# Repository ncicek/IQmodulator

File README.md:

# IQmodulator

A low cost FPGA-based platform for generating RF signals.
It is implemented with more discrete components than a typical SDR with an "all in one" RF transceiver chip. For example the quadrature double-balanced mixer uses hand-wound trifilar transformers.
 As such, it is intended as a learning platform to show the individual components at play.

# Description
The board is designed to plug into the Lattice MachXO3 FPGA starter board.
The FPGA generates the 10-bit baseband I and Q signals. A MAX5853 DAC generates the baseband analog signals which are filtered with a differential 7th order chebyshev. The FPGA PLL is also used to synthesize the quadrature LO which goes to the quadrature mixer in order to upconvert the baseband up to high frequency.

The RTL uses wishbone modules which are heavily based on material from [Gisselquist Technology's blog posts and sample code](https://zipcpu.com).

# PCB:

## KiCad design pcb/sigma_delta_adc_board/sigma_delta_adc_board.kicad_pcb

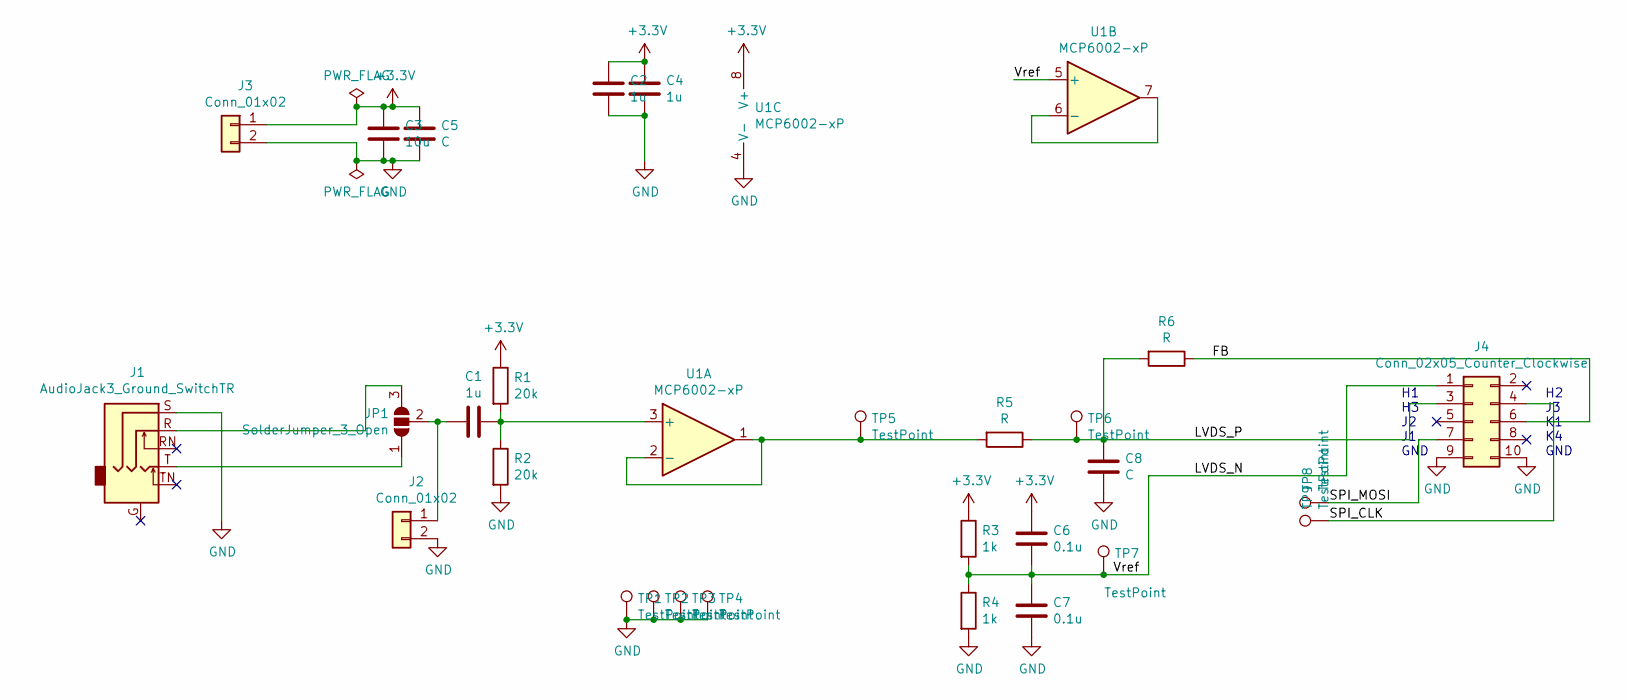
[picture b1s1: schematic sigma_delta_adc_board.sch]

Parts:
C1: 1u; C_Disc_D5.0mm_W2.5mm_P5.00mm
C2, C4: 1u; C_0805_2012Metric_Pad1.18x1.45mm_HandSolder
C3: 10u; C_Disc_D5.0mm_W2.5mm_P5.00mm
C5: C; C_Disc_D5.0mm_W2.5mm_P5.00mm
C6, C7: 0.1u; C_0805_2012Metric_Pad1.18x1.45mm_HandSolder
C8: C; C_0805_2012Metric_Pad1.18x1.45mm_HandSolder
J1: AudioJack3_Ground_SwitchTR; STX-3120-5B
J2, J3: Conn_01x02; PinHeader_1x02_P2.54mm_Vertical
J4: Conn_02x05_Counter_Clockwise; PinSocket_2x05_P2.54mm_Vertical
JP1: SolderJumper_3_Open; SolderJumper-3_P1.3mm_Open_RoundedPad1.0x1.5mm_NumberLabels
R1, R2: 20k; R_0805_2012Metric_Pad1.20x1.40mm_HandSolder
R3, R4: 1k; R_0805_2012Metric_Pad1.20x1.40mm_HandSolder
R5, R6: R; R_0805_2012Metric_Pad1.20x1.40mm_HandSolder
TP1, TP2, TP3, TP4, TP5, TP6, TP7: TestPoint; PinHeader_1x01_P2.54mm_Vertical
TP8, TP9: TestPoint; TestPoint_Pad_D1.0mm
U1: MCP6002-xP; DIP-8_W7.62mm

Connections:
+3V3: C2.2, C3.1, C4.2, C5.1, C6.2, J3.1, R1.1, R3.1, U1.8 (V+)
/FB: J4.6, R6.1
/LVDS_N: C6.1, C7.2, J4.1, R3.2, R4.1, TP7.1, U1.5 (+)
/LVDS_P: C8.2, J4.3, R5.1, R6.2, TP6.1
/SPI_CLK: J4.4, TP9.1
/SPI_MOSI: J4.7, TP8.1
GND: C2.1, C3.2, C4.1, C5.2, C7.1, C8.1, J1.S, J2.2, J3.2, J4.9, J4.10, R2.2, R4.2, TP1.1, TP2.1, TP3.1, TP4.1, U1.4 (V-)
unnamed: C1.1, R1.2, R2.1, U1.3 (+)
unnamed: C1.2, J2.1, JP1.2 (C)
unnamed: J1.R, JP1.3 (B)
unnamed: J1.T, JP1.1 (A)
unnamed: R5.2, TP5.1, U1.1, U1.2 (-)
unnamed: U1.6 (-), U1.7

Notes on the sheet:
H1 H3 J2 J1 GND
H2 J3 K1 K4 GND

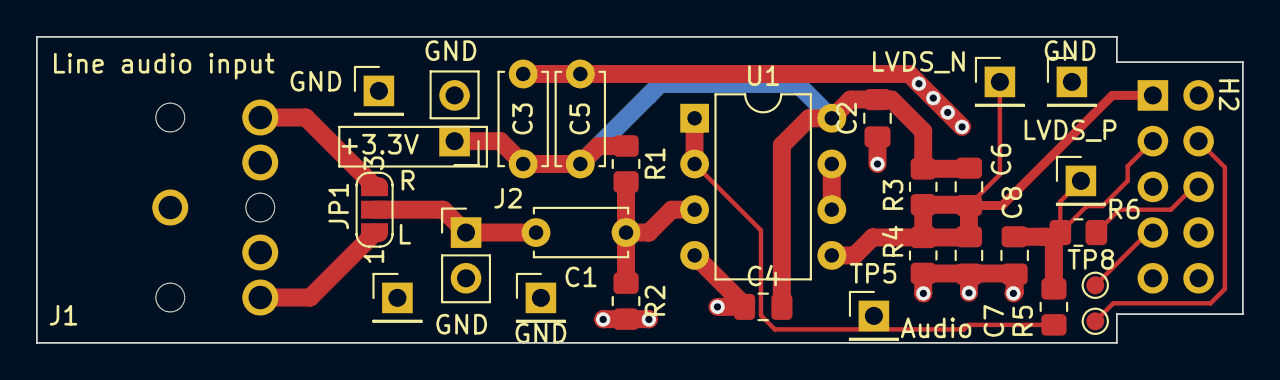
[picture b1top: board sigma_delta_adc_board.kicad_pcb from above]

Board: 2 copper layers, 67.0 x 17.0 mm, 29 parts (1 on the bottom side), 13 nets.

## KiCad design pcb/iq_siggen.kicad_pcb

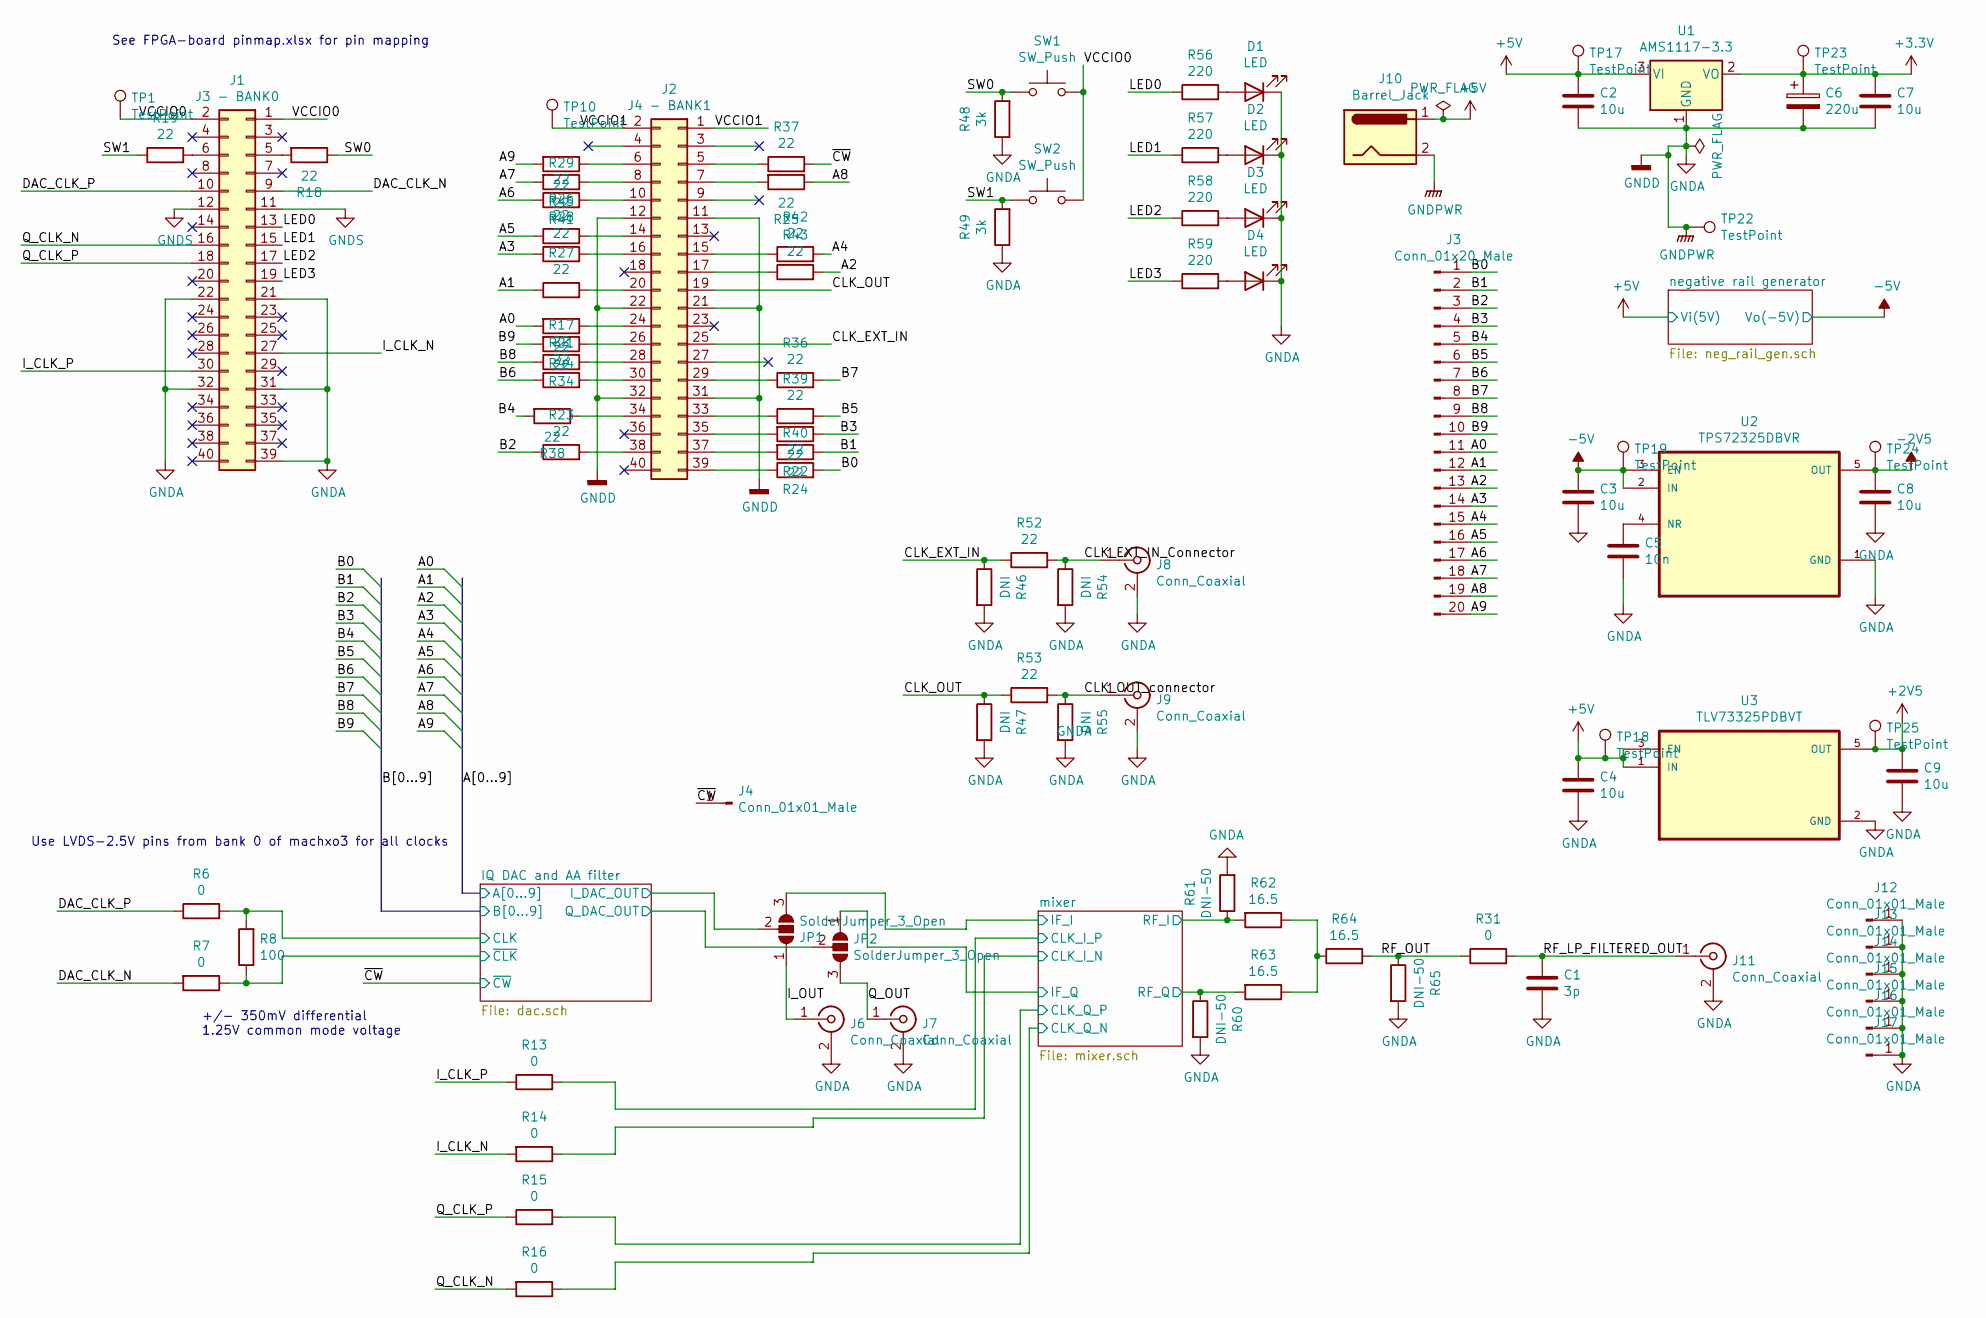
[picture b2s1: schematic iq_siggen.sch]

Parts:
C1: 3p; C_0603_1608Metric
C2, C3, C4, C7, C8, C9: 10u; C_0603_1608Metric; LCSC C19702
C5: 10n; C_0603_1608Metric; LCSC C57112
C6: 220u; CP_EIA-7343-43_Kemet-X_Pad2.25x2.55mm_HandSolder; LCSC C7231
D1, D2, D3, D4: LED; LED_0805_2012Metric_Pad1.15x1.40mm_HandSolder; LCSC C34499
J1: J3 - BANK0; PinHeader_2x20_P2.54mm_Vertical
J2: J4 - BANK1; PinHeader_2x20_P2.54mm_Vertical
J3: Conn_01x20_Male; PinHeader_1x20_P2.54mm_Vertical
J4, J12, J13, J14, J15, J16, J17: Conn_01x01_Male; PinHeader_1x01_P2.54mm_Vertical
J6, J7, J8, J9, J11: Conn_Coaxial; SMA_Samtec_SMA-J-P-X-ST-EM1_EdgeMount_withSTEP
J10: Barrel_Jack; BarrelJack_Horizontal
JP1, JP2: SolderJumper_3_Open; 50ohm_solder_jumper
R6, R7, R13, R14, R15, R16, R31: 0; R_0603_1608Metric; LCSC C21189
R8: 100; R_0603_1608Metric; LCSC C22775
R17, R18, R19, R21, R22, R23, R24, R25, R26, R27, R28, R29, R34, R36, R37, R38, R39, R40, R41, R42, R43, R44, R45, R52, R53: 22; R_0603_1608Metric; LCSC C23345
R46, R47, R54, R55: DNI; R_0603_1608Metric
R48, R49: 3k; R_0603_1608Metric; LCSC C4211
R56, R57, R58, R59: 220; R_0603_1608Metric; LCSC C22962
R60, R61, R65: DNI-50; R_0603_1608Metric
R62, R63, R64: 16.5; R_0603_1608Metric; LCSC C12054
SW1, SW2: SW_Push; SW_PUSH_6mm_H5mm
TP1, TP10, TP17, TP18, TP19, TP22, TP23, TP24, TP25: TestPoint; TestPoint_Pad_D1.5mm
U1: AMS1117-3.3; SOT-223-3_TabPin2; LCSC C6186
U2: TPS72325DBVR; SOT-23-5_HandSoldering; LCSC C69932
U3: TLV73325PDBVT; SOT-23-5_HandSoldering

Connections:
+2V5: C9.1, TP25.1, U3.5 (OUT); also elsewhere on the board
+3V3: C6.1, C7.1, TP23.1, U1.2 (VO); also elsewhere on the board
+5V: C2.1, C4.1, J10.1, TP17.1, TP18.1, U1.3 (VI), U3.1 (IN), U3.3 (EN); also elsewhere on the board
-2V5: C8.1, TP24.1, U2.5 (OUT); also elsewhere on the board
-5V: C3.1, TP19.1, U2.2 (IN), U2.3 (EN); also elsewhere on the board
/A0: J3.11, R44.2; also elsewhere on the board
/A1: J3.12, R27.1; also elsewhere on the board
/A2: J3.13, R43.2; also elsewhere on the board
/A3: J3.14, R28.1; also elsewhere on the board
/A4: J3.15, R42.2; also elsewhere on the board
/A5: J3.16, R26.1; also elsewhere on the board
/A6: J3.17, R29.1; also elsewhere on the board
/A7: J3.18, R41.2; also elsewhere on the board
/A8: J3.19, R25.1; also elsewhere on the board
/A9: J3.20, R45.2; also elsewhere on the board
/B0: J3.1, R40.2; also elsewhere on the board
/B1: J3.2, R24.1; also elsewhere on the board
/B2: J3.3, R23.1; also elsewhere on the board
/B3: J3.4, R22.1; also elsewhere on the board
/B4: J3.5, R38.2; also elsewhere on the board
/B5: J3.6, R39.2; also elsewhere on the board
/B6: J3.7, R21.1; also elsewhere on the board
/B7: J3.8, R36.2; also elsewhere on the board
/B8: J3.9, R17.1; also elsewhere on the board
/B9: J3.10, R34.2; also elsewhere on the board
/CLK_EXT_IN: J2.25, R46.1, R52.1
/CLK_EXT_IN_Connector: J8.1 (In), R52.2, R54.1
/CLK_OUT: J2.19, R47.1, R53.1
/CLK_OUT_connector: J9.1 (In), R53.2, R55.1
/DAC_CLK_N: J1.9, R7.2
/DAC_CLK_P: J1.10, R6.1
/IQ DAC and AA filter/CLK: R6.2, R8.2; also elsewhere on the board
/IQ DAC and AA filter/I_DAC_OUT: JP1.2 (C); also elsewhere on the board
/IQ DAC and AA filter/Q_DAC_OUT: JP2.2 (C); also elsewhere on the board
/IQ DAC and AA filter/~CLK: R7.1, R8.1; also elsewhere on the board
/I_CLK_N: J1.27, R14.2
/I_CLK_P: J1.30, R13.1
/I_OUT: J6.1 (In), JP1.1 (A)
/LED0: J1.13, R56.1
/LED1: J1.15, R57.1
/LED2: J1.17, R58.1
/LED3: J1.19, R59.1
/Q_CLK_N: J1.16, R16.2
/Q_CLK_P: J1.18, R15.1
/Q_OUT: J7.1 (In), JP2.3 (B)
/RF_LP_FILTERED_OUT: C1.1, J11.1 (In), R31.2
/RF_OUT: R31.1, R64.2, R65.1
/SW0: R18.1, R48.2, SW1.1
/SW1: R19.1, R49.2, SW2.1
/VCCIO0: J1.1, J1.2, SW1.2, SW2.2, TP1.1
/VCCIO1: J2.1, J2.2, TP10.1
/mixer/CLK_I_N: R14.1; also elsewhere on the board
/mixer/CLK_I_P: R13.2; also elsewhere on the board
/mixer/CLK_Q_N: R16.1; also elsewhere on the board
/mixer/CLK_Q_P: R15.2; also elsewhere on the board
/mixer/IF_I: JP1.3 (B); also elsewhere on the board
/mixer/IF_Q: JP2.1 (A); also elsewhere on the board
/mixer/RF_I: R61.1, R62.2; also elsewhere on the board
/mixer/RF_Q: R60.1, R63.2; also elsewhere on the board
/~CW: J4.1, R37.2; also elsewhere on the board
GNDA: C1.2, C2.2, C3.2, C4.2, C5.2, C6.2, C7.2, C8.2, C9.2, D1.1 (K), D2.1 (K), D3.1 (K), D4.1 (K), J1.11, J1.12, J1.21, J1.22, J1.31, J1.32, J1.39, J2.11, J2.12, J2.21, J2.22, J2.31, J2.32, J6.2 (Ext), J7.2 (Ext), J8.2 (Ext), J9.2 (Ext), J10.2, J11.2 (Ext), J12.1, J13.1, J14.1, J15.1, J16.1, J17.1, R46.2, R47.2, R48.1, R49.1, R54.2, R55.2, R60.2, R61.2, R65.2, TP22.1, U1.1 (GND), U2.1 (GND), U3.2 (GND); also elsewhere on the board
unnamed: C5.1, U2.4 (NR)
unnamed: D1.2 (A), R56.2
unnamed: D2.2 (A), R57.2
unnamed: D3.2 (A), R58.2
unnamed: D4.2 (A), R59.2
unnamed: J1.5, R18.2
unnamed: J1.6, R19.2
unnamed: J2.5, R37.1
unnamed: J2.6, R45.1
unnamed: J2.7, R25.2
unnamed: J2.8, R41.1
unnamed: J2.10, R29.2
unnamed: J2.14, R26.2
unnamed: J2.15, R42.1
unnamed: J2.16, R28.2
unnamed: J2.17, R43.1
unnamed: J2.20, R27.2
unnamed: J2.24, R44.1
unnamed: J2.26, R34.1
unnamed: J2.28, R17.2
unnamed: J2.29, R36.1
unnamed: J2.30, R21.2
unnamed: J2.33, R39.1
unnamed: J2.34, R38.1
unnamed: J2.35, R22.2
unnamed: J2.37, R24.2
unnamed: J2.38, R23.2
unnamed: J2.39, R40.1
unnamed: R62.1, R63.1, R64.1

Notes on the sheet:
Use LVDS-2.5V pins from bank 0 of machxo3 for all clocks
See FPGA-board pinmap.xlsx for pin mapping
+/- 350mV differential 1.25V common mode voltage

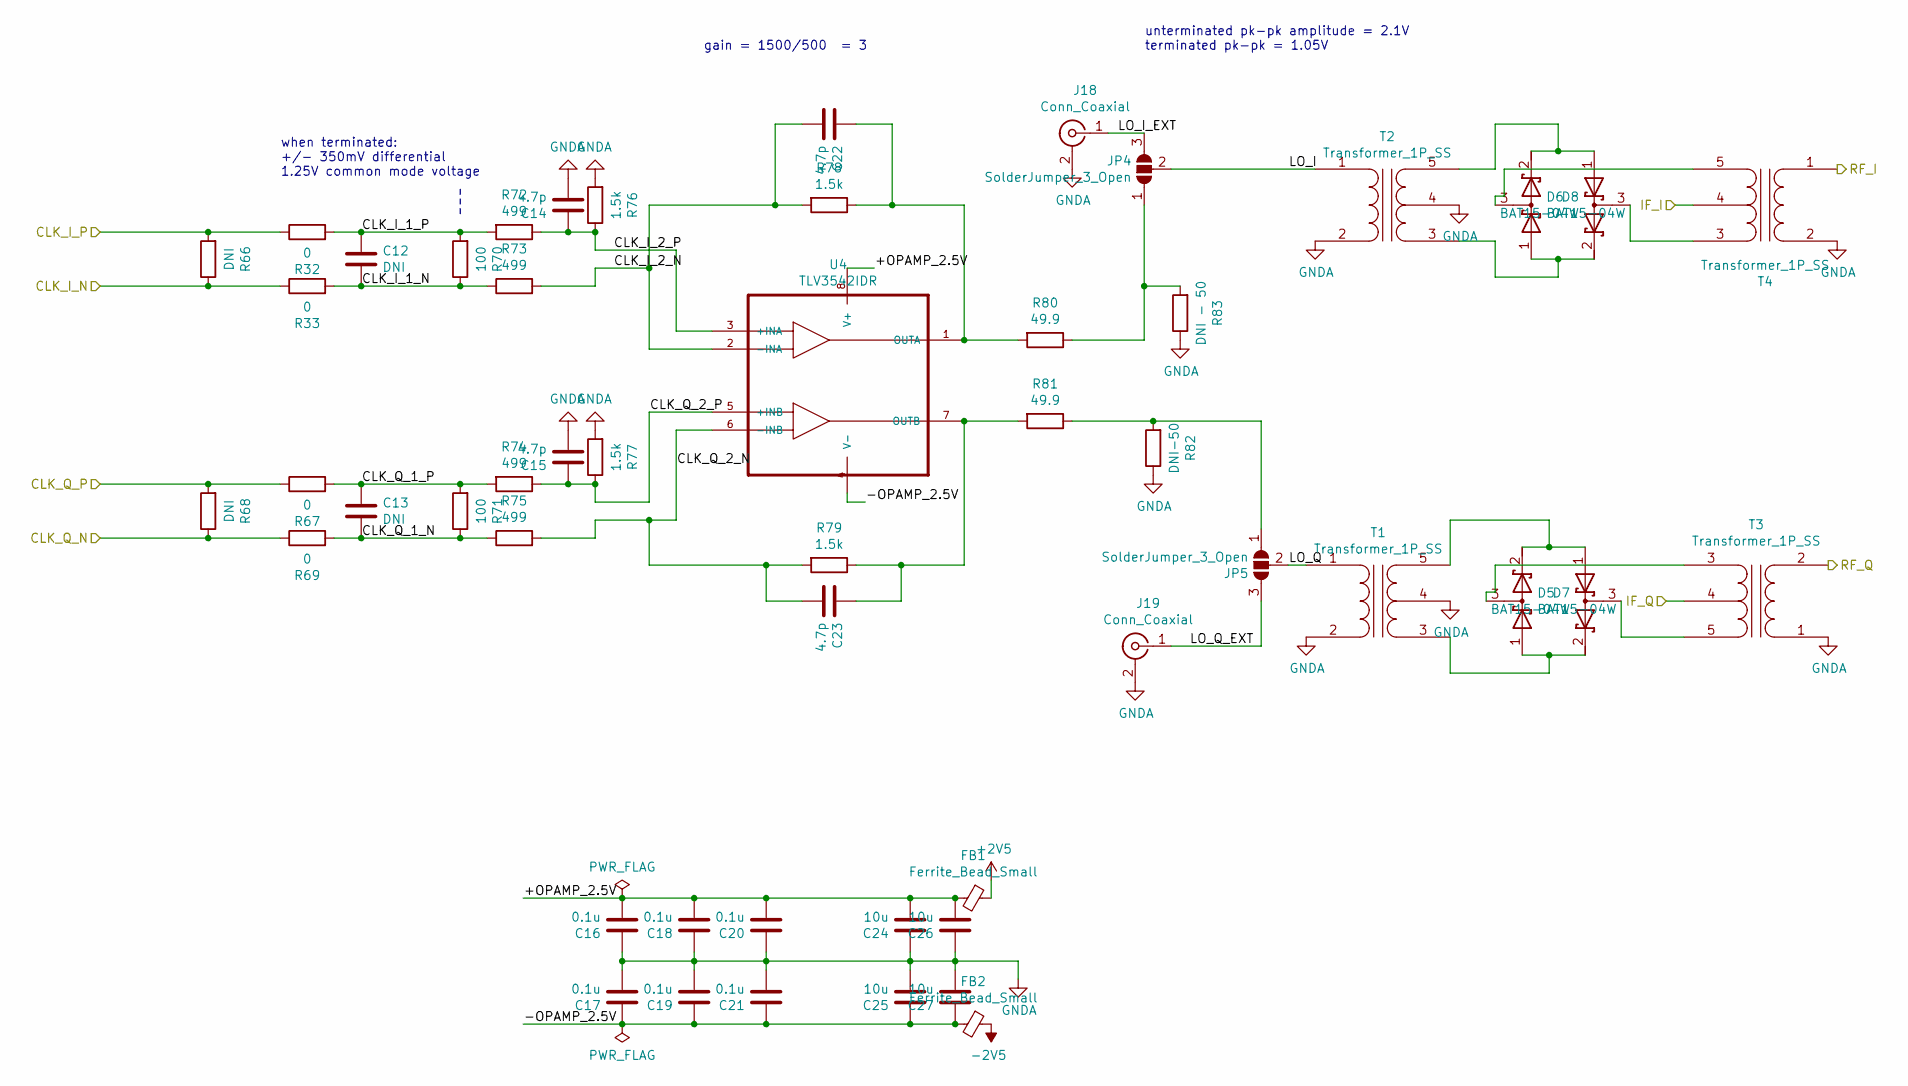
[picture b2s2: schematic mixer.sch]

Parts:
C12, C13: DNI; C_0603_1608Metric
C14, C15, C22, C23: 4.7p; C_0603_1608Metric; LCSC C1669
C16, C17, C18, C19, C20, C21: 0.1u; C_0603_1608Metric; LCSC C14663
C24, C25, C26, C27: 10u; C_0603_1608Metric; LCSC C19702
D5, D6, D7, D8: BAT15-04W; SOT-323_SC-70_Handsoldering
FB1, FB2: Ferrite_Bead_Small; L_0805_2012Metric_Pad1.05x1.20mm_HandSolder; LCSC C19330
J18, J19: Conn_Coaxial; SMA_Samtec_SMA-J-P-X-ST-EM1_EdgeMount_withSTEP
JP4, JP5: SolderJumper_3_Open; 50ohm_solder_jumper
R32, R33, R67, R69: 0; R_0603_1608Metric; LCSC C21189
R66, R68: DNI; R_0603_1608Metric
R70, R71: 100; R_0603_1608Metric; LCSC C22775
R72, R73, R74, R75: 499; R_0603_1608Metric; LCSC C23065
R76, R77, R78, R79: 1.5k; R_0603_1608Metric; LCSC C22843
R80, R81: 49.9; R_0603_1608Metric; LCSC C23185
R82: DNI-50; R_0603_1608Metric
R83: DNI - 50; R_0603_1608Metric
T1, T2, T3, T4: Transformer_1P_SS; trifilar_wound_toroidal_rf_transformer
U4: TLV3542IDR; SOIC-8_3.9x4.9mm_P1.27mm

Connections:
+2V5: FB1.1; also elsewhere on the board
-2V5: FB2.1; also elsewhere on the board
/mixer/+OPAMP_2.5V: C16.2, C18.2, C20.2, C24.2, C26.2, FB1.2, U4.8 (V+)
/mixer/-OPAMP_2.5V: C17.1, C19.1, C21.1, C25.1, C27.1, FB2.2, U4.4 (V-)
/mixer/CLK_I_1_N: C12.2, R33.2, R70.1, R73.1
/mixer/CLK_I_1_P: C12.1, R32.2, R70.2, R72.2
/mixer/CLK_I_2_N: C22.2, R73.2, R78.2, U4.2 (-INA)
/mixer/CLK_I_2_P: C14.1, R72.1, R76.1, U4.3 (+INA)
/mixer/CLK_I_N: R33.1, R66.1; also elsewhere on the board
/mixer/CLK_I_P: R32.1, R66.2; also elsewhere on the board
/mixer/CLK_Q_1_N: C13.2, R69.2, R71.1, R75.1
/mixer/CLK_Q_1_P: C13.1, R67.2, R71.2, R74.2
/mixer/CLK_Q_2_N: C23.2, R75.2, R79.2, U4.6 (-INB)
/mixer/CLK_Q_2_P: C15.1, R74.1, R77.1, U4.5 (+INB)
/mixer/CLK_Q_N: R68.1, R69.1; also elsewhere on the board
/mixer/CLK_Q_P: R67.1, R68.2; also elsewhere on the board
/mixer/IF_I: T4.4 (SC); also elsewhere on the board
/mixer/IF_Q: T3.4 (SC); also elsewhere on the board
/mixer/LO_I: JP4.2 (C), T2.1 (AA)
/mixer/LO_I_EXT: J18.1 (In), JP4.3 (B)
/mixer/LO_Q: JP5.2 (C), T1.1 (AA)
/mixer/LO_Q_EXT: J19.1 (In), JP5.3 (B)
/mixer/RF_I: T4.1 (AA); also elsewhere on the board
/mixer/RF_Q: T3.2 (AB); also elsewhere on the board
GNDA: C14.2, C15.2, C16.1, C17.2, C18.1, C19.2, C20.1, C21.2, C24.1, C25.2, C26.1, C27.2, J18.2 (Ext), J19.2 (Ext), R76.2, R77.2, R82.1, R83.1, T1.2 (AB), T1.4 (SC), T2.2 (AB), T2.4 (SC), T3.1 (AA), T4.2 (AB); also elsewhere on the board
unnamed: C22.1, R78.1, R80.2, U4.1 (OUTA)
unnamed: C23.1, R79.1, R81.2, U4.7 (OUTB)
unnamed: D5.1 (A), D7.2 (K), T1.3 (SA)
unnamed: D5.2 (K), D7.1 (A), T1.5 (SB)
unnamed: D5.3 (common), T3.3 (SA)
unnamed: D6.1 (A), D8.2 (K), T2.3 (SA)
unnamed: D6.2 (K), D8.1 (A), T2.5 (SB)
unnamed: D6.3 (common), T4.5 (SB)
unnamed: D7.3 (common), T3.5 (SB)
unnamed: D8.3 (common), T4.3 (SA)
unnamed: JP4.1 (A), R80.1, R83.2
unnamed: JP5.1 (A), R81.1, R82.2

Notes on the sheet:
when terminated: +/- 350mV differential 1.25V common mode voltage
gain = 1500/500 = 3
unterminated pk-pk amplitude = 2.1V terminated pk-pk = 1.05V

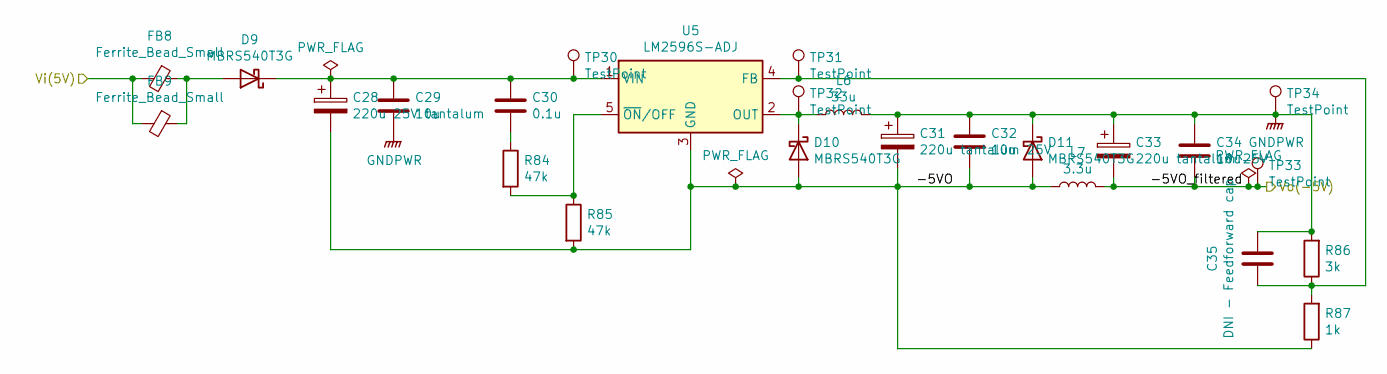
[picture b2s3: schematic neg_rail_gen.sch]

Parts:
C28: 220u 25V tantalum; CP_EIA-7343-43_Kemet-X_Pad2.25x2.55mm_HandSolder; LCSC C7231
C29, C32, C34: 10u; C_0603_1608Metric; LCSC C19702
C30: 0.1u; C_0603_1608Metric; LCSC C14663
C31, C33: 220u tantalum 25V; CP_EIA-7343-43_Kemet-X_Pad2.25x2.55mm_HandSolder; LCSC C7231
C35: DNI - Feedforward cap; C_0805_2012Metric_Pad1.15x1.40mm_HandSolder
D9, D10, D11: MBRS540T3G; D_SMB_Handsoldering; LCSC C14651
FB8, FB9: Ferrite_Bead_Small; L_0805_2012Metric_Pad1.05x1.20mm_HandSolder; LCSC C19330
L6: 33u; L_Bourns_SRR1260
L7: 3.3u; L_Axial_L9.5mm_D4.0mm_P12.70mm_Horizontal_Fastron_SMCC
R84, R85: 47k; R_0603_1608Metric; LCSC C25819
R86: 3k; R_0603_1608Metric; LCSC C4211
R87: 1k; R_0603_1608Metric; LCSC C21190
TP30, TP31, TP32, TP33, TP34: TestPoint; TestPoint_Pad_D1.5mm
U5: LM2596S-ADJ; TO-263-5_TabPin3

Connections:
+5V: FB8.2, FB9.2; also elsewhere on the board
-5V: C33.2, C34.1, L7.2, TP33.1; also elsewhere on the board
/negative rail generator/-5VO: C28.2, C31.2, C32.1, D10.2 (A), D11.2 (A), L7.1, R85.2, R87.1, U5.3 (GND)
GNDA: C29.2, C31.1, C32.2, C33.1, C34.2, C35.2, D11.1 (K), L6.2, R86.2, TP34.1; also elsewhere on the board
unnamed: C28.1, C29.1, C30.1, D9.1 (K), TP30.1, U5.1 (VIN)
unnamed: C30.2, R84.1
unnamed: C35.1, R86.1, R87.2, TP31.1, U5.4 (FB)
unnamed: D9.2 (A), FB8.1, FB9.1
unnamed: D10.1 (K), L6.1, TP32.1, U5.2 (OUT)
unnamed: R84.2, R85.1, U5.5 (~ON~/OFF)

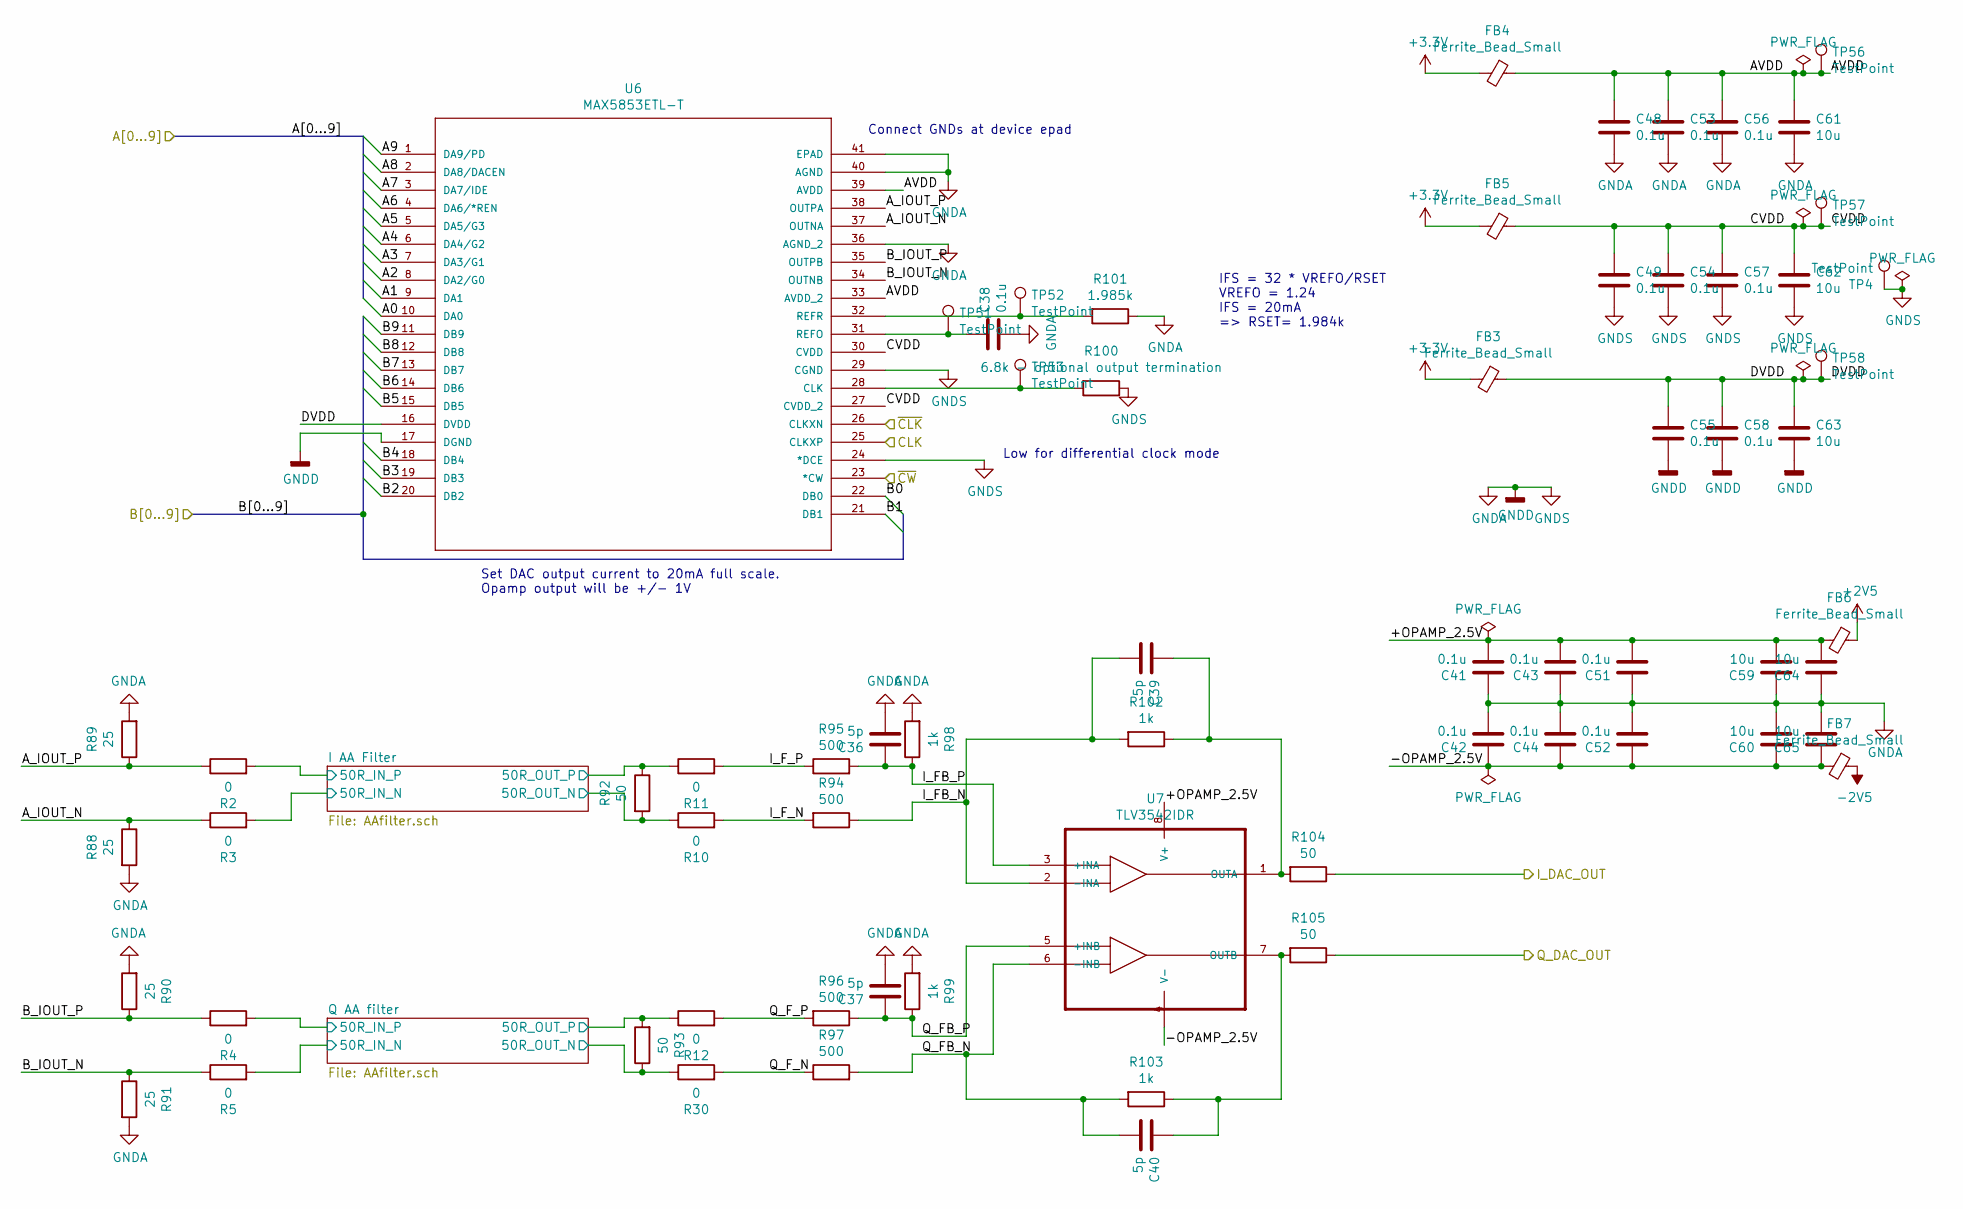
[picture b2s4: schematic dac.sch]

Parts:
C36, C37, C39, C40: 5p; C_0603_1608Metric
C38, C41, C42, C43, C44, C48, C49, C51, C52, C53, C54, C55, C56, C57, C58: 0.1u; C_0603_1608Metric
C59, C60, C61, C62, C63, C64, C65: 10u; C_0603_1608Metric
FB3, FB4, FB5, FB6, FB7: Ferrite_Bead_Small; L_0805_2012Metric_Pad1.05x1.20mm_HandSolder
R2, R3, R4, R5, R10, R11, R12, R30: 0; R_0603_1608Metric
R88, R89, R90, R91: 25; R_0603_1608Metric
R92, R93, R104, R105: 50; R_0603_1608Metric
R94, R95, R96, R97: 500; R_0603_1608Metric
R98, R99, R102, R103: 1k; R_0603_1608Metric
R100: 6.8k - optional output termination; R_0603_1608Metric
R101: 1.985k; R_0603_1608Metric
TP4: TestPoint; TestPoint_Pad_D1.5mm
TP51, TP52, TP53, TP56, TP57, TP58: TestPoint; TestPoint_Pad_D1.0mm
U6: MAX5853ETL-T; qfn_max5853
U7: TLV3542IDR; SOIC-8_3.9x4.9mm_P1.27mm

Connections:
+2V5: FB6.1; also elsewhere on the board
+3V3: FB3.2, FB4.2, FB5.2; also elsewhere on the board
-2V5: FB7.1; also elsewhere on the board
/A0: U6.10 (DA0); also elsewhere on the board
/A1: U6.9 (DA1); also elsewhere on the board
/A2: U6.8 (DA2/G0); also elsewhere on the board
/A3: U6.7 (DA3/G1); also elsewhere on the board
/A4: U6.6 (DA4/G2); also elsewhere on the board
/A5: U6.5 (DA5/G3); also elsewhere on the board
/A6: U6.4 (DA6/*REN); also elsewhere on the board
/A7: U6.3 (DA7/IDE); also elsewhere on the board
/A8: U6.2 (DA8/DACEN); also elsewhere on the board
/A9: U6.1 (DA9/PD); also elsewhere on the board
/B0: U6.22 (DB0); also elsewhere on the board
/B1: U6.21 (DB1); also elsewhere on the board
/B2: U6.20 (DB2); also elsewhere on the board
/B3: U6.19 (DB3); also elsewhere on the board
/B4: U6.18 (DB4); also elsewhere on the board
/B5: U6.15 (DB5); also elsewhere on the board
/B6: U6.14 (DB6); also elsewhere on the board
/B7: U6.13 (DB7); also elsewhere on the board
/B8: U6.12 (DB8); also elsewhere on the board
/B9: U6.11 (DB9); also elsewhere on the board
/IQ DAC and AA filter/+OPAMP_2.5V: C41.2, C43.2, C51.2, C59.2, C64.2, FB6.2, U7.8 (V+)
/IQ DAC and AA filter/-OPAMP_2.5V: C42.1, C44.1, C52.1, C60.1, C65.1, FB7.2, U7.4 (V-)
/IQ DAC and AA filter/AVDD: C48.1, C53.1, C56.1, C61.1, FB4.1, TP56.1, U6.33 (AVDD_2), U6.39 (AVDD)
/IQ DAC and AA filter/A_IOUT_N: R3.1, R88.1, U6.37 (OUTNA)
/IQ DAC and AA filter/A_IOUT_P: R2.1, R89.1, U6.38 (OUTPA)
/IQ DAC and AA filter/B_IOUT_N: R5.1, R91.1, U6.34 (OUTNB)
/IQ DAC and AA filter/B_IOUT_P: R4.1, R90.1, U6.35 (OUTPB)
/IQ DAC and AA filter/CLK: U6.25 (CLKXP); also elsewhere on the board
/IQ DAC and AA filter/CVDD: C49.1, C54.1, C57.1, C62.1, FB5.1, TP57.1, U6.27 (CVDD_2), U6.30 (CVDD)
/IQ DAC and AA filter/DVDD: C55.1, C58.1, C63.1, FB3.1, TP58.1, U6.16 (DVDD)
/IQ DAC and AA filter/I AA Filter/50R_IN_N: R3.2; also elsewhere on the board
/IQ DAC and AA filter/I AA Filter/50R_IN_P: R2.2; also elsewhere on the board
/IQ DAC and AA filter/I AA Filter/50R_OUT_N: R10.1, R92.2; also elsewhere on the board
/IQ DAC and AA filter/I AA Filter/50R_OUT_P: R11.1, R92.1; also elsewhere on the board
/IQ DAC and AA filter/I_DAC_OUT: R104.1; also elsewhere on the board
/IQ DAC and AA filter/I_FB_N: C39.2, R94.1, R102.2, U7.2 (-INA)
/IQ DAC and AA filter/I_FB_P: C36.1, R95.2, R98.1, U7.3 (+INA)
/IQ DAC and AA filter/I_F_N: R10.2, R94.2
/IQ DAC and AA filter/I_F_P: R11.2, R95.1
/IQ DAC and AA filter/Q AA filter/50R_IN_N: R5.2; also elsewhere on the board
/IQ DAC and AA filter/Q AA filter/50R_IN_P: R4.2; also elsewhere on the board
/IQ DAC and AA filter/Q AA filter/50R_OUT_N: R30.1, R93.1; also elsewhere on the board
/IQ DAC and AA filter/Q AA filter/50R_OUT_P: R12.1, R93.2; also elsewhere on the board
/IQ DAC and AA filter/Q_DAC_OUT: R105.1; also elsewhere on the board
/IQ DAC and AA filter/Q_FB_N: C40.2, R97.2, R103.2, U7.6 (-INB)
/IQ DAC and AA filter/Q_FB_P: C37.1, R96.1, R99.1, U7.5 (+INB)
/IQ DAC and AA filter/Q_F_N: R30.2, R97.1
/IQ DAC and AA filter/Q_F_P: R12.2, R96.2
/IQ DAC and AA filter/~CLK: U6.26 (CLKXN); also elsewhere on the board
/~CW: U6.23 (*CW); also elsewhere on the board
GNDA: C36.2, C37.2, C38.2, C41.1, C42.2, C43.1, C44.2, C48.2, C49.2, C51.1, C52.2, C53.2, C54.2, C55.2, C56.2, C57.2, C58.2, C59.1, C60.2, C61.2, C62.2, C63.2, C64.1, C65.2, R88.2, R89.2, R90.2, R91.2, R98.2, R99.2, R100.1, R101.1, TP4.1, U6.17 (DGND), U6.24 (*DCE), U6.29 (CGND), U6.36 (AGND_2), U6.40 (AGND), U6.41 (EPAD); also elsewhere on the board
unnamed: C38.1, TP51.1, U6.31 (REFO)
unnamed: C39.1, R102.1, R104.2, U7.1 (OUTA)
unnamed: C40.1, R103.1, R105.2, U7.7 (OUTB)
unnamed: R100.2, TP53.1, U6.28 (CLK)
unnamed: R101.2, TP52.1, U6.32 (REFR)

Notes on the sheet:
Connect GNDs at device epad
Set DAC output current to 20mA full scale. Opamp output will be +/- 1V
Low for differential clock mode
IFS = 32 * VREFO/RSET VREFO = 1.24 IFS = 20mA => RSET= 1.984k

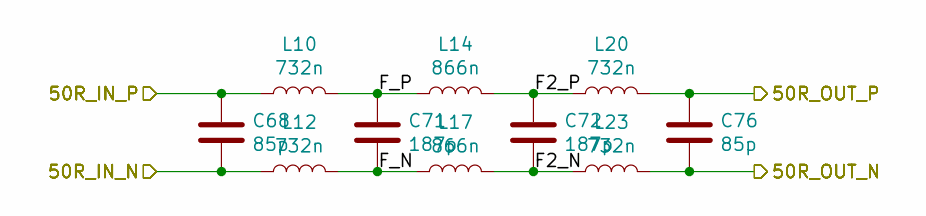
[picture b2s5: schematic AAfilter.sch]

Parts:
C68, C76: 85p; C_0603_1608Metric
C71, C72: 187p; C_0603_1608Metric
L10, L12, L20, L23: 732n; L_0603_1608Metric
L14, L17: 866n; L_0603_1608Metric

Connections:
/IQ DAC and AA filter/I AA Filter/50R_IN_N: C68.2, L12.1; also elsewhere on the board
/IQ DAC and AA filter/I AA Filter/50R_IN_P: C68.1, L10.1; also elsewhere on the board
/IQ DAC and AA filter/I AA Filter/50R_OUT_N: C76.2, L23.2; also elsewhere on the board
/IQ DAC and AA filter/I AA Filter/50R_OUT_P: C76.1, L20.2; also elsewhere on the board
/IQ DAC and AA filter/I AA Filter/F2_N: C72.2, L17.2, L23.1
/IQ DAC and AA filter/I AA Filter/F2_P: C72.1, L14.2, L20.1
/IQ DAC and AA filter/I AA Filter/F_N: C71.2, L12.2, L17.1
/IQ DAC and AA filter/I AA Filter/F_P: C71.1, L10.2, L14.1
